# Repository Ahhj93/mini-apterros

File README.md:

# Mini-Apterros
> [!Note]
> Fusée expérimentale du projet Perseus du CNES

Ce dépôt rassemble la conception et la documentation de la mini-fusée Apterros.
L'objectif est de centraliser les ressources techniques pour faciliter le travail de l'équipe.

## Arborescence principale
- `docs/` : documents de référence du projet (présentations, notices, procédures LabVIEW et MATLAB).
- `src/` : ressources techniques et développement (hardware, code Jetson Nano et éléments associés).
- `src/hardware/` : fichiers de conception PCB (versions actuelles et anciennes).
- `src/jetson-nano/` : backend, site web et tests liés à la partie embarquée Jetson Nano.
- `references_composants.md` : référence des composants utilisés dans le projet.
- `CONTRIBUTING.md` : guide de contribution pour participer au dépôt.

## Contributeurs
|  |  |  |  | 
| :---: | :---: | :---: | :---: | :---: |
| [@Ahhj93](https://github.com/Ahhj93) | [@sblikeice](https://github.com/sblikeice) | [@Margaux-Lapl](https://github.com/Margaux-Lapl) | [@julien0305](https://github.com/julien0305) | [@JoaoCerq](https://github.com/JoaoCerq) |
| Bryan-Sowanna ING | Sara BAILLEUL | Margaux LAPLANTE | Julien THOMAS | João Pedro DA SILVA CERQUIERA |

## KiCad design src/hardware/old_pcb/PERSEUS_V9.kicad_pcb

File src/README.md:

Ce dossier contient les fichiers sources du projet Mini-Apterros.

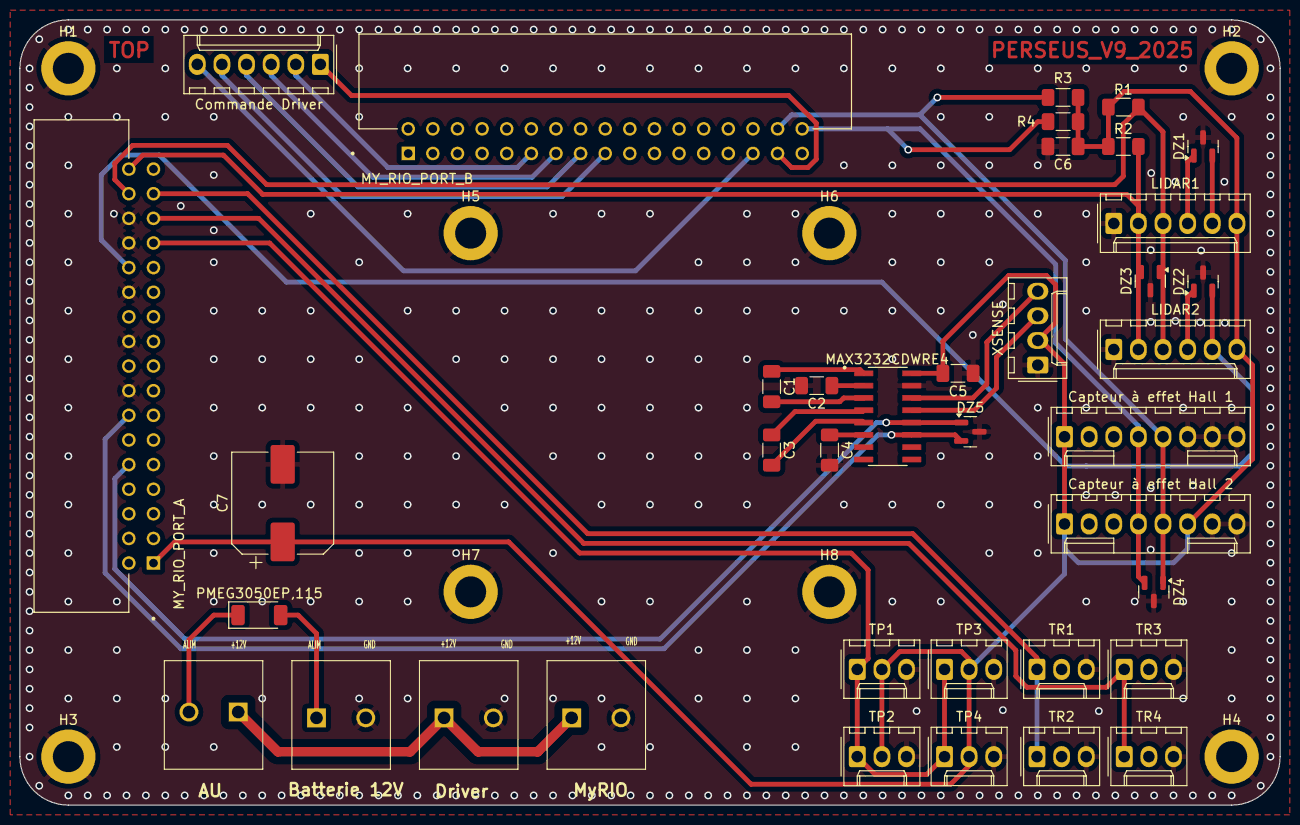
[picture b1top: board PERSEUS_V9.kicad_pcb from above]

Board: 2 copper layers, 130.0 x 81.0 mm, 46 parts (0 on the bottom side), 32 nets.

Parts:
AU: RELAIS; 1711725
Batterie 12V: BATTERIE; 1711725
C1: 0.047 uF; C_1206_3216Metric_Pad1.33x1.80mm_HandSolder
C2, C3, C4: 0.033 uF; C_1206_3216Metric_Pad1.33x1.80mm_HandSolder
C5: 0.1 uF; C_1206_3216Metric_Pad1.33x1.80mm_HandSolder
C6: 10uF; C_1206_3216Metric_Pad1.33x1.80mm_HandSolder
C7: 680 uF; CP_Elec_10x10
Capteur à effet Hall 1: Capteur à effet Hall 1; Molex_KK-254_AE-6410-08A_1x08_P2.54mm_Vertical
Capteur à effet Hall 2: Capteur à effet Hall 2; Molex_KK-254_AE-6410-08A_1x08_P2.54mm_Vertical
Commande Driver: Conn_01x06; Molex_KK-254_AE-6410-06A_1x06_P2.54mm_Vertical
DZ1, DZ2, DZ3, DZ4, DZ5: VHW; SOT-23
Driver: MOTEUR_CC; 1711725
H1, H2, H3, H4, H5, H6, H7, H8: MountingHole_Pad; MountingHole_3.2mm_M3_DIN965_Pad
LIDAR1: LIDAR_I2C; Molex_KK-254_AE-6410-06A_1x06_P2.54mm_Vertical
LIDAR2: LIDAR2_I2C; Molex_KK-254_AE-6410-06A_1x06_P2.54mm_Vertical
MAX3232CDWRE4: MAX3232CDWRE4; SOIC127P600X175-16N
MY_RIO_PORT_A: MY_RIO_PORT_A; TE_103311-7
MY_RIO_PORT_B: MY_RIO_PORT_B; TE_103311-7
MyRIO: MY_RIO; 1711725
PMEG3050EP,115: PMEG3050EP,115; D_SOD-128
R1, R2, R3, R4: 4.7k; R_1206_3216Metric_Pad1.30x1.75mm_HandSolder
TP1: TP1; Molex_KK-254_AE-6410-03A_1x03_P2.54mm_Vertical
TP2: TP2; Molex_KK-254_AE-6410-03A_1x03_P2.54mm_Vertical
TP3: TP3; Molex_KK-254_AE-6410-03A_1x03_P2.54mm_Vertical
TP4: TP4; Molex_KK-254_AE-6410-03A_1x03_P2.54mm_Vertical
TR1: TR1; Molex_KK-254_AE-6410-03A_1x03_P2.54mm_Vertical
TR2: TR2; Molex_KK-254_AE-6410-03A_1x03_P2.54mm_Vertical
TR3: TR3; Molex_KK-254_AE-6410-03A_1x03_P2.54mm_Vertical
TR4: TR4; Molex_KK-254_AE-6410-03A_1x03_P2.54mm_Vertical
XSENSE: XSENSE; Molex_KK-254_AE-6410-04A_1x04_P2.54mm_Vertical

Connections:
+5V: C5.2, C6.1, C7.1, Capteur à effet Hall 1.1, Capteur à effet Hall 2.1, Capteur à effet Hall 2.6, LIDAR1.6, LIDAR2.6, MAX3232CDWRE4.16 (VCC), MY_RIO_PORT_A.1, R1.1, R2.1, R3.1, R4.1, TP1.2, TP2.2, TP3.2, TP4.2, XSENSE.2
/+12V: AU.1, Driver.1, MyRIO.1
GND: Batterie 12V.2, C2.2, C4.2, C5.1, C6.2, C7.2, Capteur à effet Hall 1.6, Capteur à effet Hall 1.7, Capteur à effet Hall 1.8, Capteur à effet Hall 2.7, Capteur à effet Hall 2.8, DZ1.3 (A), DZ2.3 (A), DZ3.3 (A), DZ4.3 (A), DZ5.3 (A), Driver.2, H1.1, H2.1, H3.1, H4.1, H5.1, H6.1, H7.1, H8.1, LIDAR1.1, LIDAR2.1, MAX3232CDWRE4.15 (GND), MY_RIO_PORT_A.16, MY_RIO_PORT_A.20, MY_RIO_PORT_A.24, MY_RIO_PORT_A.28, MY_RIO_PORT_A.30, MyRIO.2, TP1.3, TP2.3, TP3.3, TP4.3, TR1.3, TR2.3, TR3.3, TR4.3, XSENSE.1
I2C_SDA: DZ3.2 (K), LIDAR1.2, LIDAR2.2, MY_RIO_PORT_A.34, R2.2
I2C_SDA_B: Capteur à effet Hall 1.4, Capteur à effet Hall 2.4, DZ4.2 (K), MY_RIO_PORT_B.34, R4.2
I2C_SDL: DZ3.1 (K), LIDAR1.3, LIDAR2.3, MY_RIO_PORT_A.32, R1.2
I2C_SDL_B: Capteur à effet Hall 1.5, Capteur à effet Hall 2.5, DZ4.1 (K), MY_RIO_PORT_B.32, R3.2
LIDAR2_4: DZ2.1 (K), LIDAR2.4
LIDAR2_5: DZ2.2 (K), LIDAR2.5, MY_RIO_PORT_A.26
LIDAR_4: DZ1.1 (K), LIDAR1.4
LIDAR_5: DZ1.2 (K), LIDAR1.5
unnamed: C1.1, MAX3232CDWRE4.1 (C1+)
unnamed: C1.2, MAX3232CDWRE4.3 (C1-)
unnamed: C3.1, MAX3232CDWRE4.4 (C2+)
unnamed: C3.2, MAX3232CDWRE4.5 (C2-)
unnamed: C2.1, MAX3232CDWRE4.2 (V+)
unnamed: C4.1, MAX3232CDWRE4.6 (V-)
unnamed: AU.2, PMEG3050EP,115.1
unnamed: Batterie 12V.1, PMEG3050EP,115.2
OUTPUT_1: Commande Driver.2, MY_RIO_PORT_B.11
OUTPUT_2: Commande Driver.3, MY_RIO_PORT_B.13
OUTPUT_3: Commande Driver.4, MY_RIO_PORT_B.15
OUTPUT_4: Commande Driver.5, MY_RIO_PORT_B.17
PWM_MOT_1: Commande Driver.1, MY_RIO_PORT_B.31
PWM_MOT_2: Commande Driver.6, MY_RIO_PORT_B.29
PWM_OPTO: MY_RIO_PORT_A.27, TP1.1, TP2.1, TP3.1, TP4.1
PWM_ROULIS_1: MY_RIO_PORT_A.31, TR1.1, TR2.1
PWM_ROULIS_2: MY_RIO_PORT_A.29, TR3.1, TR4.1
RX_3232: MAX3232CDWRE4.14 (DOUT1), XSENSE.4
TX_3232: MAX3232CDWRE4.13 (RIN1), XSENSE.3
UART_RX: DZ5.1 (K), MAX3232CDWRE4.12 (ROUT1), MY_RIO_PORT_A.10
UART_TX: DZ5.2 (K), MAX3232CDWRE4.11 (DIN1), MY_RIO_PORT_A.14
